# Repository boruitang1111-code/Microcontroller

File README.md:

# Fisher 1
This is my personal microcontroller board for the Hackclub phantom project.

This board is powered by a rp2040 microcontroller and was made to tinker with. It exist to do microcontroller things and to power other potential projects. Because of this it has one fully featured gpio pin header and easy access Bootsel and reset button.
The Fisher 1 board features a unified header with dual power and data usb ports. Meaning it has 30gpio pins in one long stretch and 2 different USB port for power and data.

# Assembly guide
1. purchase pcb.
2. purchase parts.
3. solder parts.
4. done.

# How to flash
1. plug data cable into usb-B port
2. hold down bootsel button and click reset button
3. check computer for a removable drive called RPI-RP2
4. put .uf2 file into RPI-RP2

# specs:
IC: rp2040
Storage: W25Q128 (16MB external flash)
GPIO: 30pins
Power:5v USB C
Data:Standard Micro USB

# BOM
| ID | Designator | Footprint | Quantity | Designation | Supplier and ref |
| :--- | :--- | :--- | :---: | :--- | :--- |
| 1 | C1, C2, C3, C9, C11, C12, C13, C14, C15, C16, C17 | `C_0603_1608Metric` | 11 | 100nf | |
| 2 | C4, C5 | `C_0603_1608Metric` | 2 | 15pf | |
| 3 | C6 | `C_0603_1608Metric` | 1 | 10µF | |
| 4 | C7, C8, C10 | `C_0603_1608Metric` | 3 | 1µF | |
| 5 | J1 | `USB_C_Receptacle_HRO_TYPE-C-31-M-17` | 1 | USB_C_Receptacle_PowerOnly_6P | |
| 6 | J2 | `USB_Micro-B_Amphenol_10118193-0001LF_Horizontal` | 1 | USB_B_Micro | |
| 7 | J3 | `PinHeader_1x03_P2.54mm_Vertical` | 1 | Conn_01x03_Pin | |
| 8 | J4, J5 | `PinHeader_1x30_P2.54mm_Vertical` | 2 | Conn_01x30_Pin | |
| 9 | R1, R2 | `R_0603_1608Metric` | 2 | 5100 | |
| 10 | R3, R5 | `R_0603_1608Metric` | 2 | 10k | |
| 11 | R4 | `R_0603_1608Metric` | 1 | 1k | |
| 12 | reset, SW1 | `SW_SPST_B3U-1000P` | 2 | SW_Push | |
| 13 | U1 | `QFN-56-1EP_7x7mm_P0.4mm_EP3.2x3.2mm` | 1 | RP2040 | |
| 14 | U2 | `WSON-8-1EP_8x6mm_P1.27mm_EP3.4x4.3mm` | 1 | W25Q128JVE | |
| 15 | U3 | `SOT-23-5` | 1 | AP2112K-3.3 | |
| 16 | Y1 | `Crystal_SMD_Abracon_ABM8G-4Pin_3.2x2.5mm` | 1 | Crystal_GND24 | |

# Important clarification:
i have no idea what i am doing and this has not been produced nor tested. Prototype at you own risk.

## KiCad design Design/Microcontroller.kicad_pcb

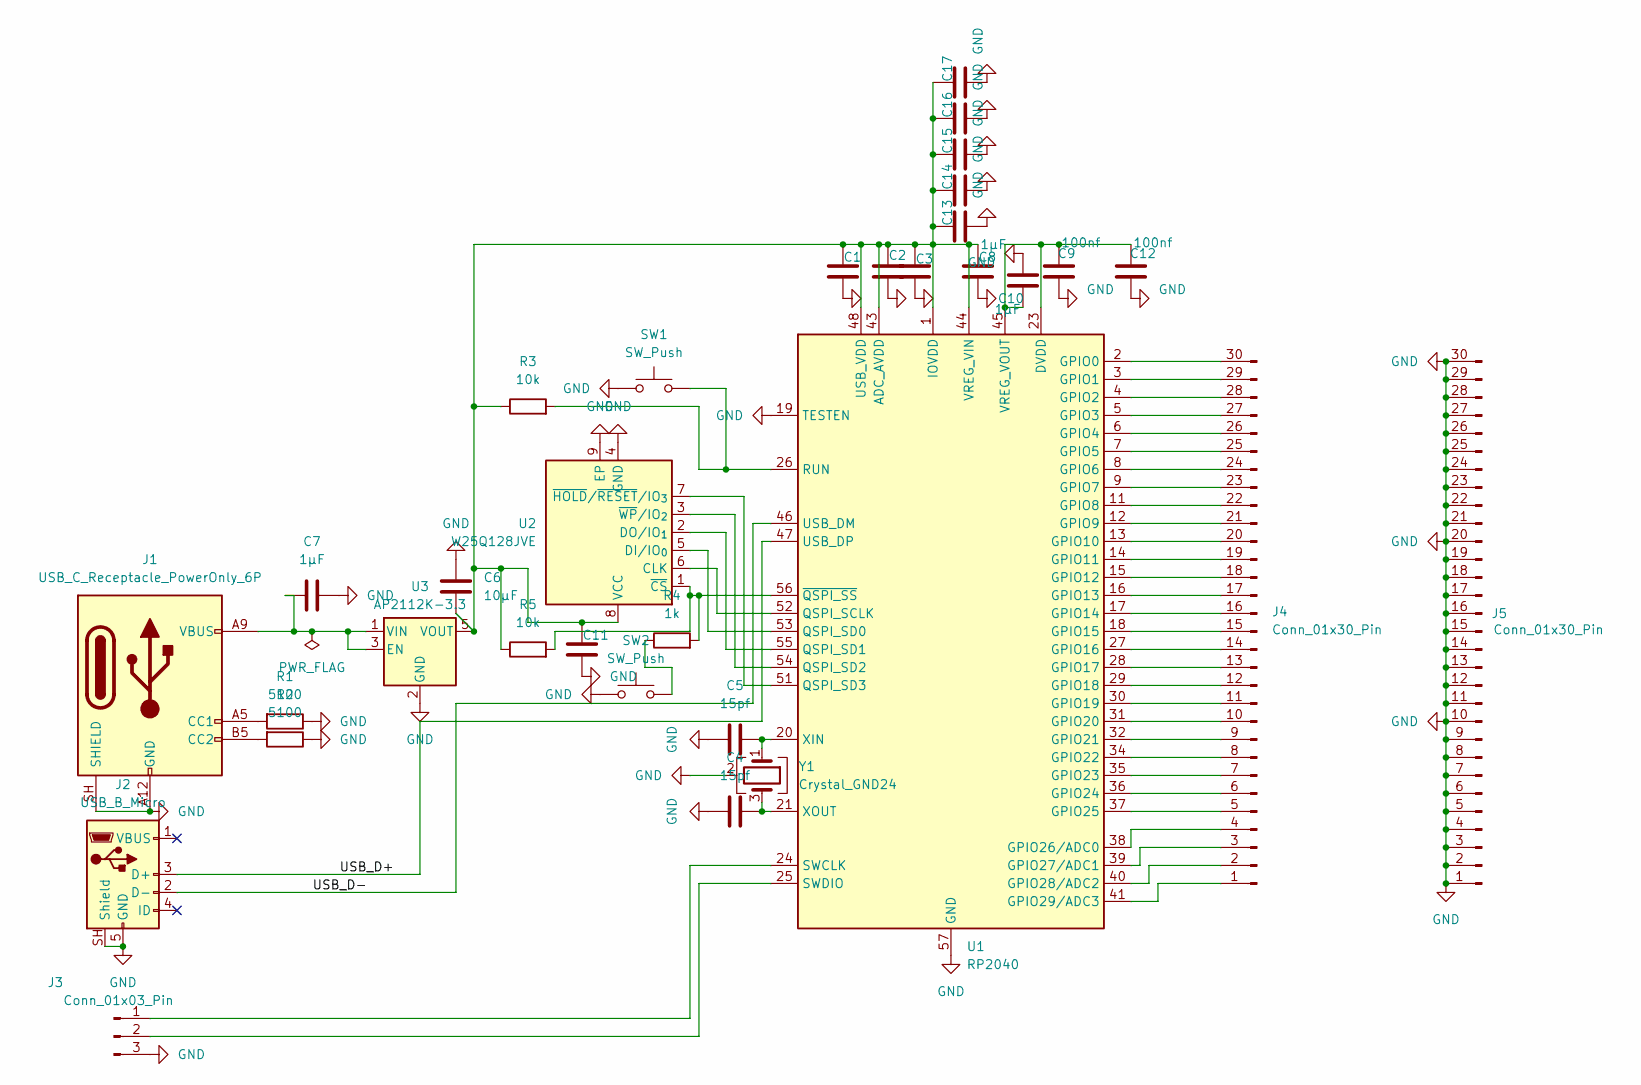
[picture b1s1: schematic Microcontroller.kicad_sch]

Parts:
C1, C2, C3, C9, C11, C12, C13, C14, C15, C16, C17: 100nf; C_0603_1608Metric
C4, C5: 15pf; C_0603_1608Metric
C6: 10µF; C_0603_1608Metric
C7, C8, C10: 1µF; C_0603_1608Metric
J1: USB_C_Receptacle_PowerOnly_6P; USB_C_Receptacle_HRO_TYPE-C-31-M-17
J2: USB_B_Micro; USB_Micro-B_Amphenol_10118193-0001LF_Horizontal
J3: Conn_01x03_Pin; PinHeader_1x03_P2.54mm_Vertical
J4, J5: Conn_01x30_Pin; PinHeader_1x30_P2.54mm_Vertical
R1, R2: 5100; R_0603_1608Metric
R3, R5: 10k; R_0603_1608Metric
R4: 1k; R_0603_1608Metric
SW1, SW2: SW_Push; SW_SPST_B3U-1000P
U1: RP2040; QFN-56-1EP_7x7mm_P0.4mm_EP3.2x3.2mm
U2: W25Q128JVE; WSON-8-1EP_8x6mm_P1.27mm_EP3.4x4.3mm
U3: AP2112K-3.3; SOT-23-5
Y1: Crystal_GND24; Crystal_SMD_Abracon_ABM8G-4Pin_3.2x2.5mm

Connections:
/USB_D+: J2.3 (D+), U1.47 (USB_DP)
/USB_D-: J2.2 (D-), U1.46 (USB_DM)
GND: C1.2, C2.2, C3.2, C4.1, C5.1, C6.1, C7.2, C8.2, C9.2, C10.2, C11.2, C12.2, C13.2, C14.2, C15.2, C16.2, C17.2, J1.A12 (GND), J1.B12 (GND), J1.SH (SHIELD), J2.5 (GND), J2.SH (Shield), J3.3, J5.1, J5.2, J5.3, J5.4, J5.5, J5.6, J5.7, J5.8, J5.9, J5.10, J5.11, J5.12, J5.13, J5.14, J5.15, J5.16, J5.17, J5.18, J5.19, J5.20, J5.21, J5.22, J5.23, J5.24, J5.25, J5.26, J5.27, J5.28, J5.29, J5.30, R1.1, R2.1, SW1.1, SW2.1, U1.19 (TESTEN), U1.57 (GND), U2.4 (GND), U2.9 (EP), U3.2 (GND), Y1.2 (G), Y1.4 (G); also elsewhere on the board
unnamed: J1.A5 (CC1), R1.2
unnamed: J1.B5 (CC2), R2.2
unnamed: J3.1, U1.24 (SWCLK)
unnamed: J3.2, U1.25 (SWDIO)
unnamed: J4.1, U1.41 (GPIO29/ADC3)
unnamed: J4.2, U1.40 (GPIO28/ADC2)
unnamed: J4.3, U1.39 (GPIO27/ADC1)
unnamed: J4.4, U1.38 (GPIO26/ADC0)
unnamed: J4.5, U1.37 (GPIO25)
unnamed: J4.6, U1.36 (GPIO24)
unnamed: J4.7, U1.35 (GPIO23)
unnamed: J4.8, U1.34 (GPIO22)
unnamed: J4.9, U1.32 (GPIO21)
unnamed: J4.10, U1.31 (GPIO20)
unnamed: J4.11, U1.30 (GPIO19)
unnamed: J4.12, U1.29 (GPIO18)
unnamed: J4.13, U1.28 (GPIO17)
unnamed: J4.14, U1.27 (GPIO16)
unnamed: J4.15, U1.18 (GPIO15)
unnamed: J4.16, U1.17 (GPIO14)
unnamed: J4.17, U1.16 (GPIO13)
unnamed: J4.18, U1.15 (GPIO12)
unnamed: J4.19, U1.14 (GPIO11)
unnamed: J4.20, U1.13 (GPIO10)
unnamed: J4.21, U1.12 (GPIO9)
unnamed: J4.22, U1.11 (GPIO8)
unnamed: J4.23, U1.9 (GPIO7)
unnamed: J4.24, U1.8 (GPIO6)
unnamed: J4.25, U1.7 (GPIO5)
unnamed: J4.26, U1.6 (GPIO4)
unnamed: J4.27, U1.5 (GPIO3)
unnamed: J4.28, U1.4 (GPIO2)
unnamed: J4.29, U1.3 (GPIO1)
unnamed: J4.30, U1.2 (GPIO0)
unnamed 37: R4.1, SW2.2; also elsewhere on the board
unnamed: C1.1, C2.1, C3.1, C6.2, C8.1, C11.1, C13.1, C14.1, C15.1, C16.1, C17.1, R3.1, R5.1, U1.1 (IOVDD), U1.10 (IOVDD), U1.22 (IOVDD), U1.33 (IOVDD), U1.42 (IOVDD), U1.43 (ADC_AVDD), U1.44 (VREG_VIN), U1.48 (USB_VDD), U1.49 (IOVDD), U2.8 (VCC), U3.5 (VOUT)
unnamed: U1.52 (QSPI_SCLK), U2.6 (CLK)
unnamed: U1.53 (QSPI_SD0), U2.5 (DI/IO_{0})
unnamed: U1.55 (QSPI_SD1), U2.2 (DO/IO_{1})
unnamed: U1.54 (QSPI_SD2), U2.3 (~WP/IO_{2})
unnamed: U1.51 (QSPI_SD3), U2.7 (~HOLD/~RESET/IO_{3})
unnamed: R3.2, SW1.2, U1.26 (RUN)
unnamed: C9.1, C10.1, C12.1, U1.23 (DVDD), U1.45 (VREG_VOUT), U1.50 (DVDD)
unnamed: C5.2, U1.20 (XIN), Y1.1
unnamed: C4.2, U1.21 (XOUT), Y1.3
unnamed: R4.2, R5.2, U1.56 (~QSPI_SS), U2.1 (~CS)
unnamed: C7.1, J1.A9 (VBUS), J1.B9 (VBUS), U3.1 (VIN), U3.3 (EN)

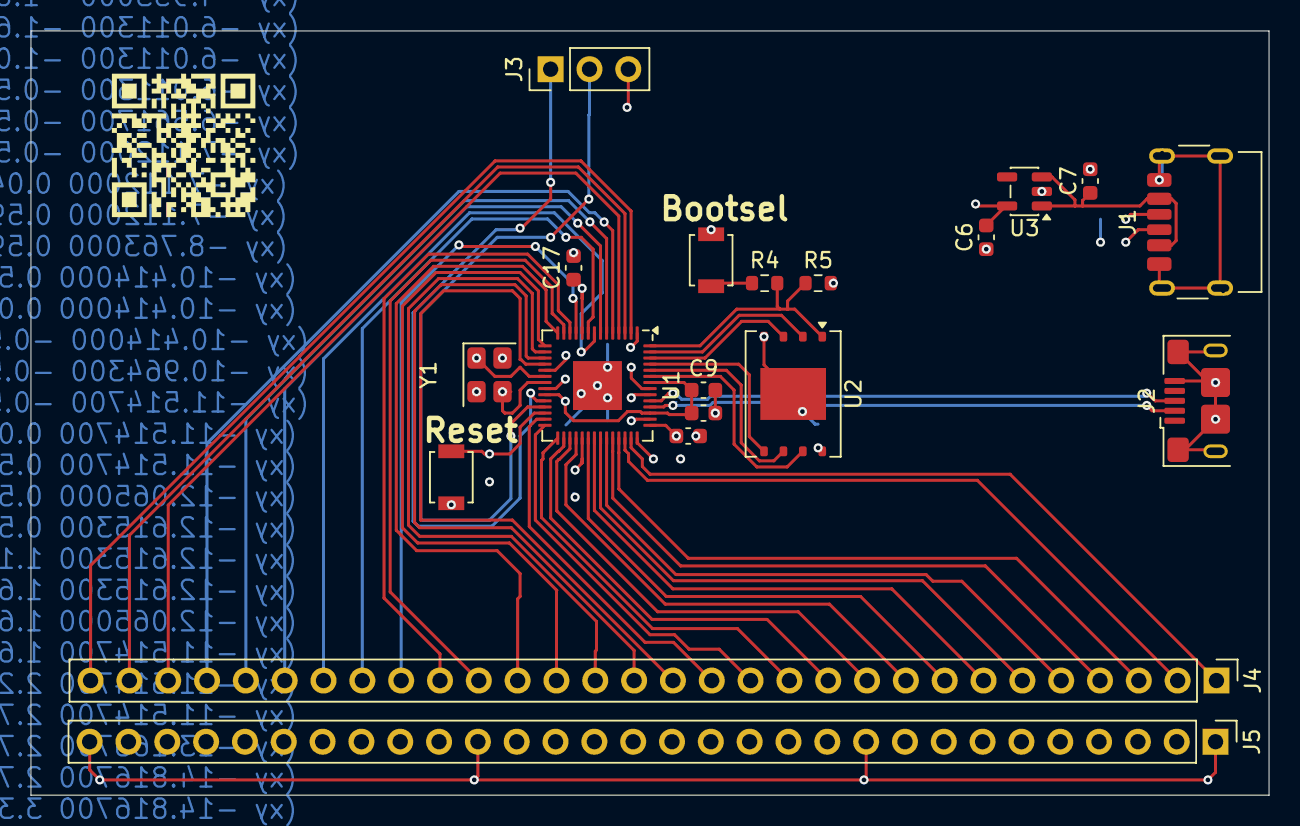
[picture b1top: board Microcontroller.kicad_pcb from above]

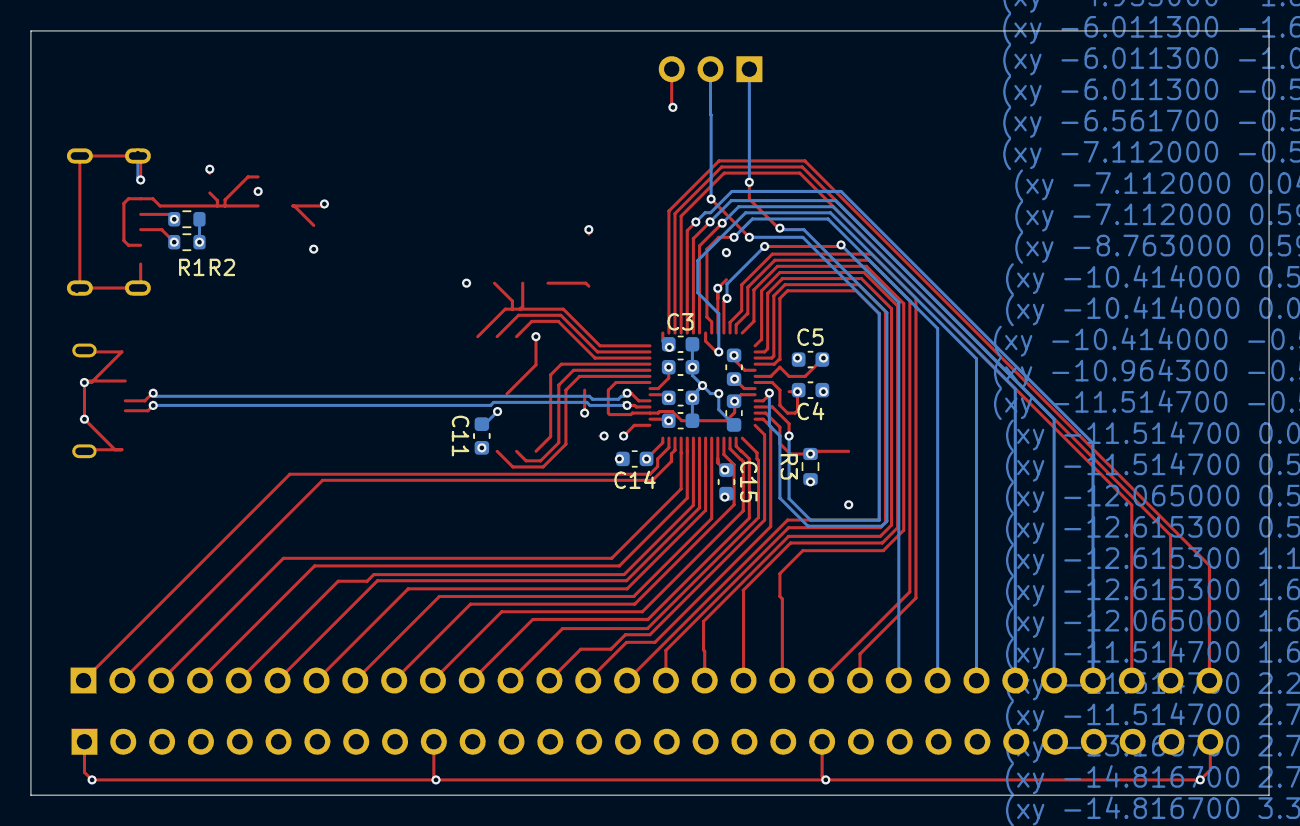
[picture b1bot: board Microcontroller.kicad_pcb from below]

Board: 4 copper layers, 81.0 x 50.0 mm, 33 parts (14 on the bottom side), 50 nets.

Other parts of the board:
reset: SW_Push; SW_SPST_B3U-1000P

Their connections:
GND: reset.1; also elsewhere on the board
unnamed 37: reset.2; also elsewhere on the board
